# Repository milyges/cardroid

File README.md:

# cardroid
Odroid C2 and STM32F103 based, car computer for Renault Megane

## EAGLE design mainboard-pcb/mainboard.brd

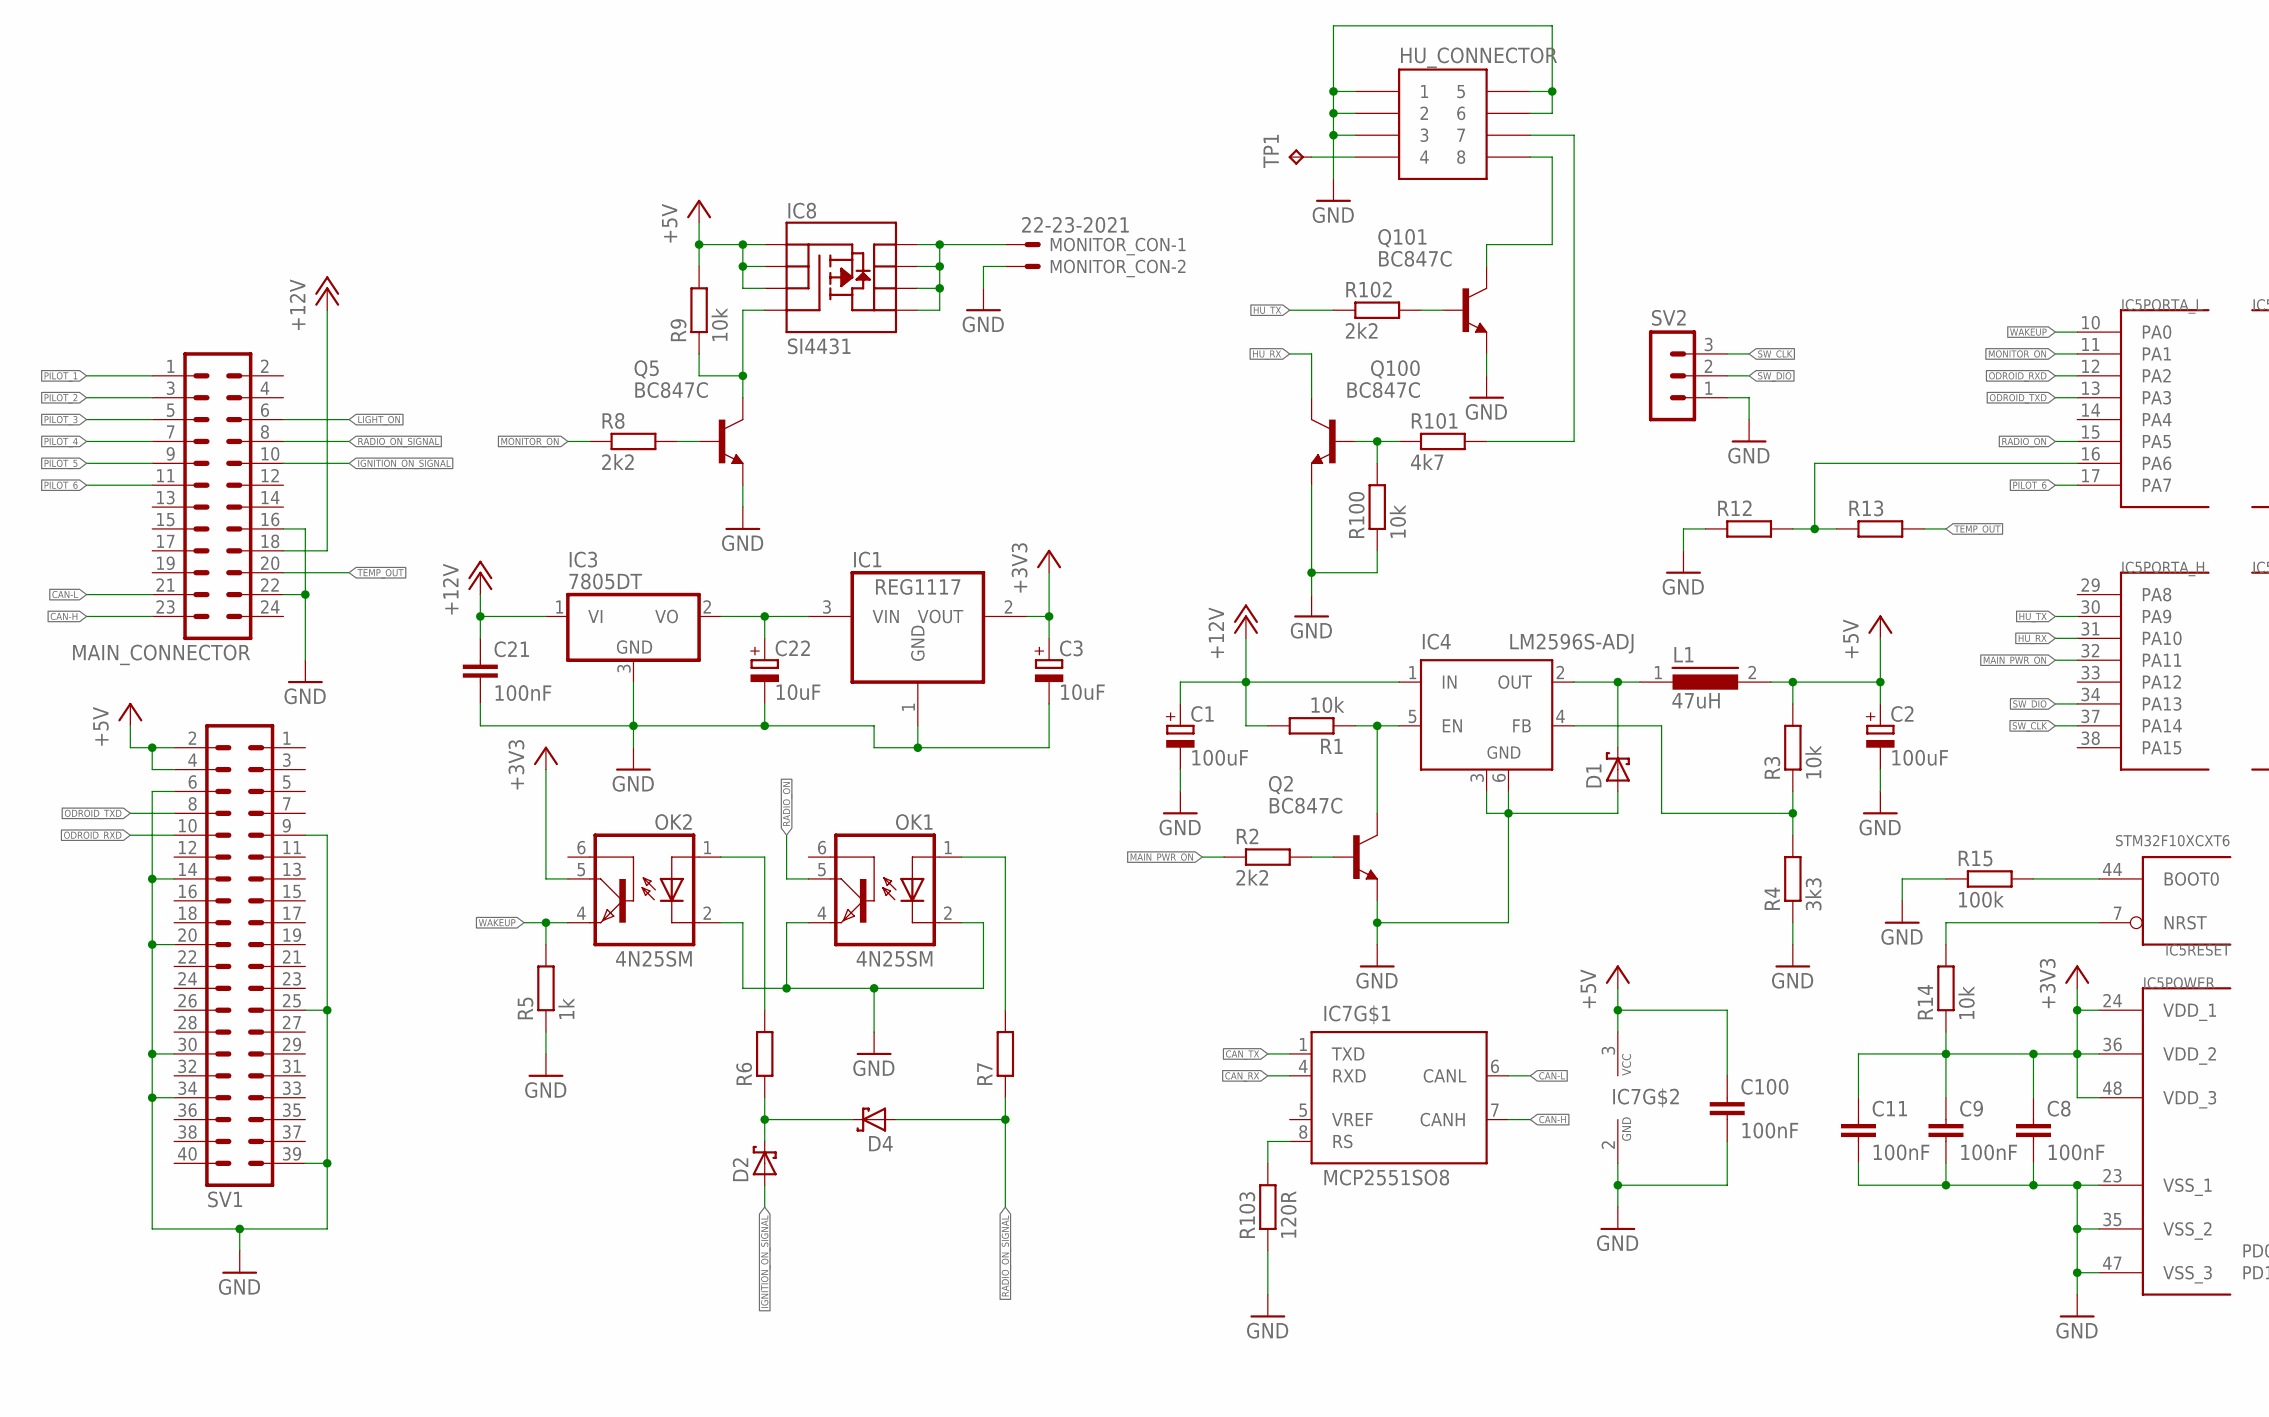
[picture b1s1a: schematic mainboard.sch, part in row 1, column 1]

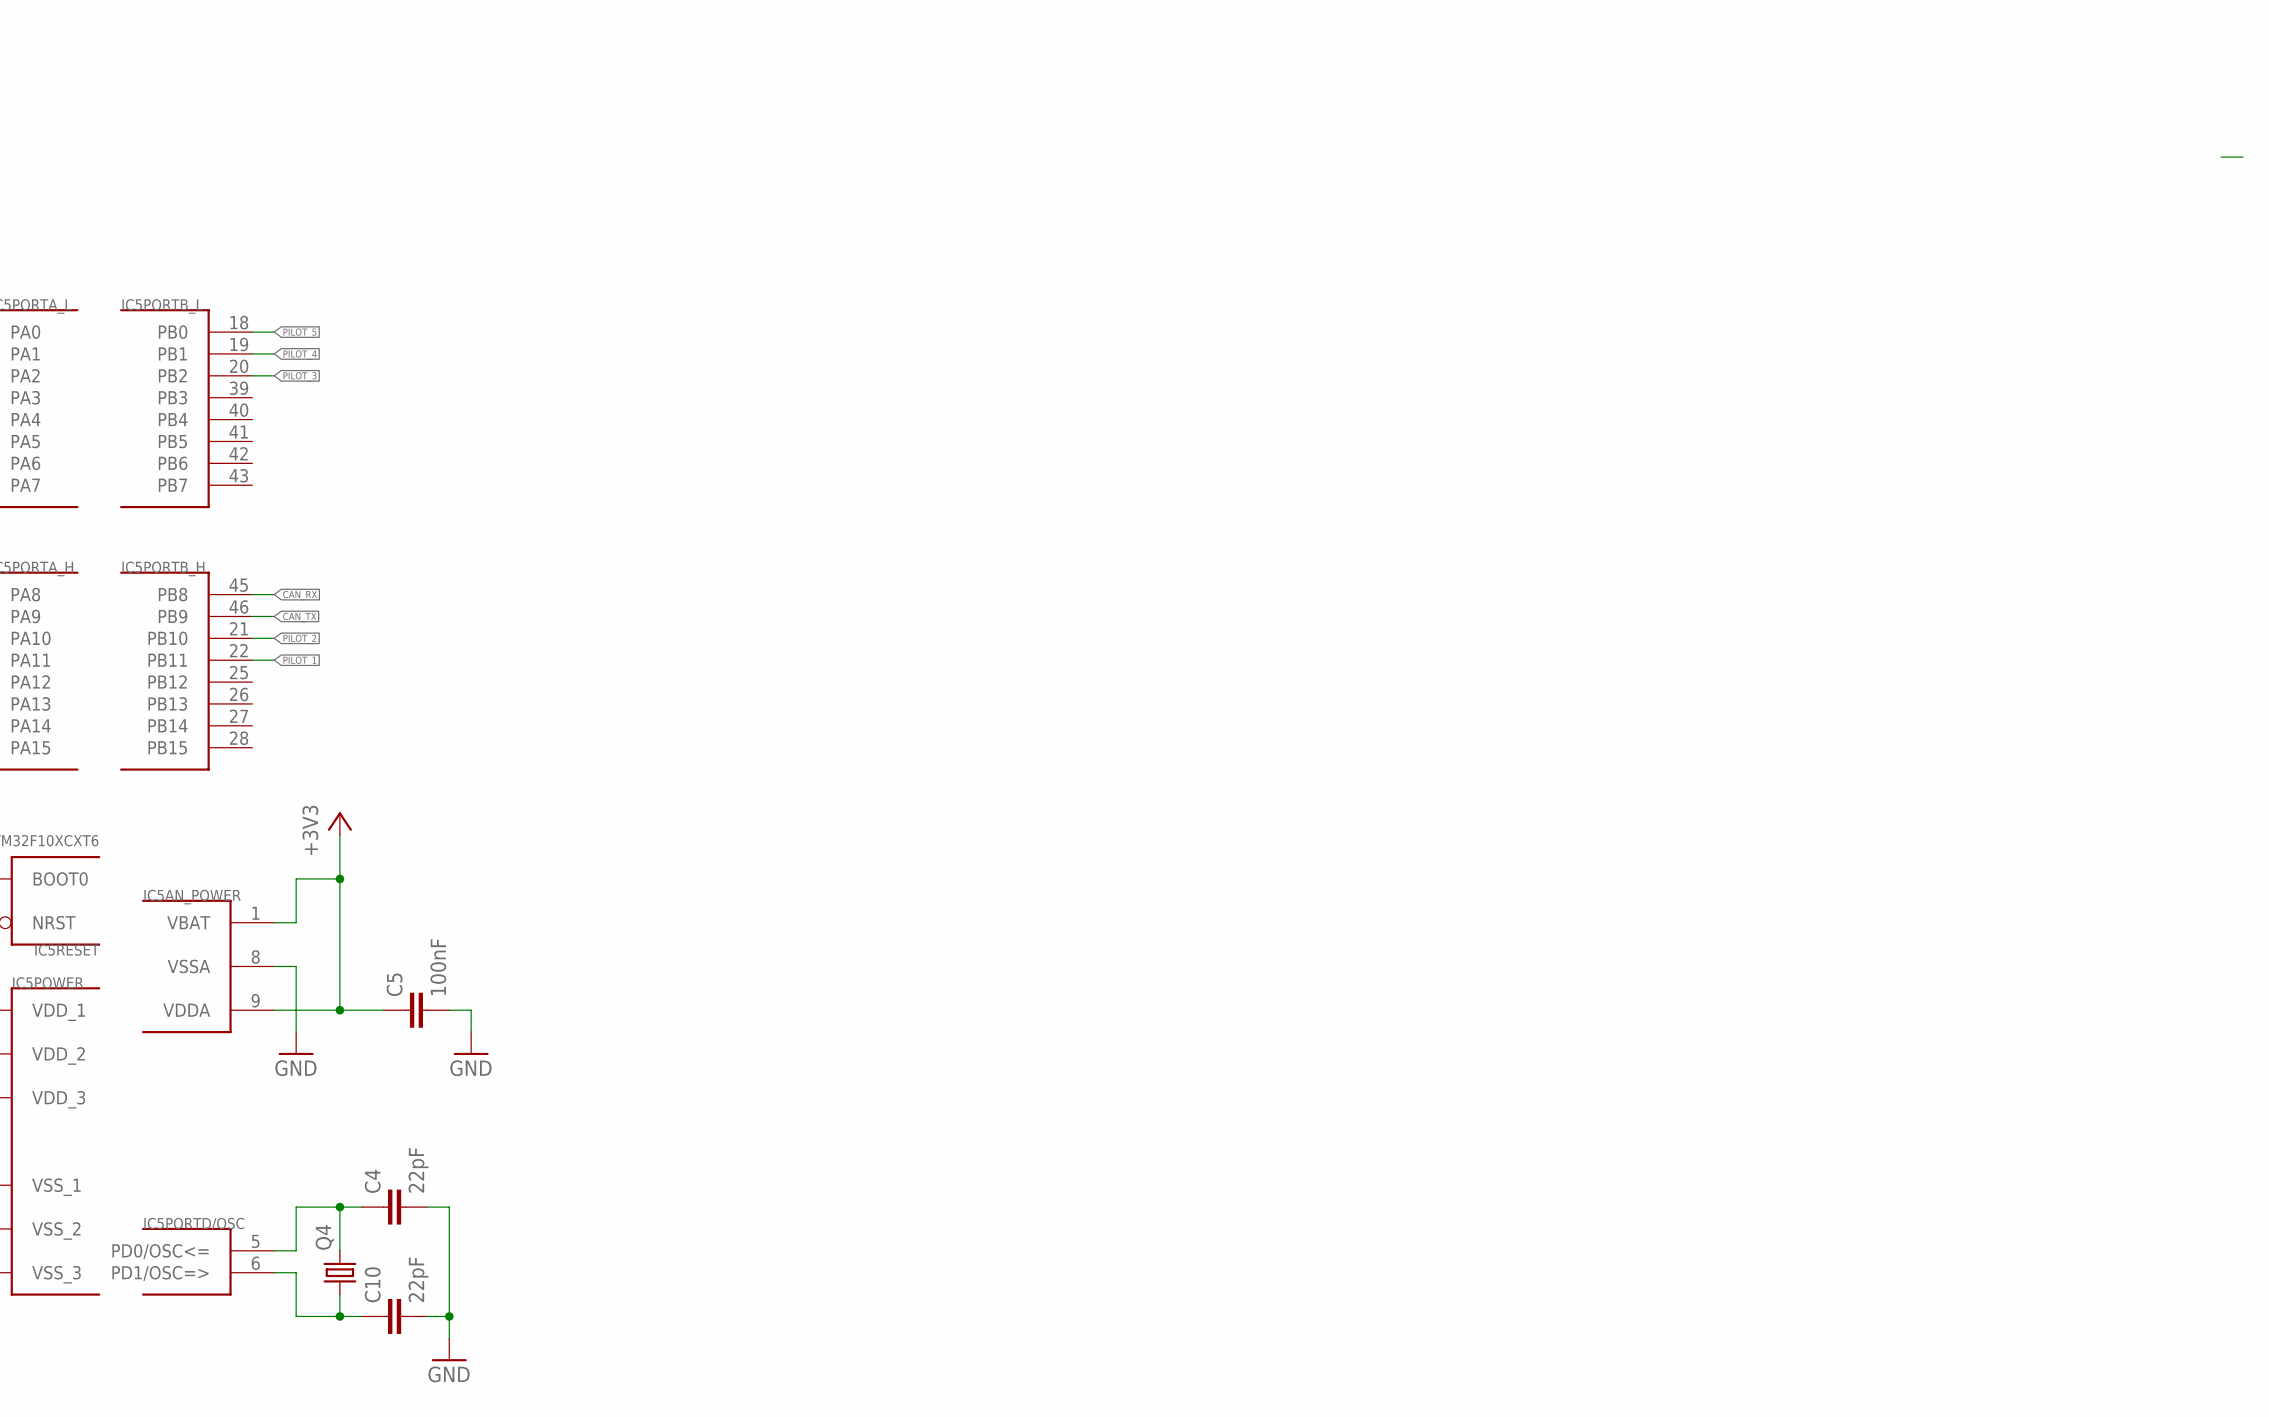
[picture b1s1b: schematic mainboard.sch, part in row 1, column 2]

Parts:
C1, C2: 100uF; 153CLV-0807
C3, C22: 10uF; SMC_A
C4, C10: 22pF; C0805
C5: 100nF; C0603
C8, C9, C11, C21, C100: 100nF; C0805
D1, D2, D4: SCHOTTKY-DIODESMD; SMB
HU_CONNECTOR: MRX56908CV; MRX56908
IC1: REG1117; SOT223
IC3: 7805DT; TO252
IC4: LM2596S-ADJ; TO263-5
IC5: STM32F10XCXT6; TQFP48
IC7: MCP2551SO8; SO08
IC8: SI4431; SO08
L1: 47uH; DR125
MAIN_CONNECTOR: MA12-2
MONITOR_CON: 22-23-2021
OK1, OK2: 4N25SM; DIL6-SMD
Q2, Q5, Q100, Q101: BC847C; SOT23-BEC
Q4: CRYSTALHC49UP; HC49UP
R1, R3, R9, R14, R100: 10k; M0805
R2, R8, R102: 2k2; M0805
R4: 3k3; M0805
R5: 1k; M0805
R6, R7, R12, R13: R-EU_M0805; M0805
R15: 100k; M0805
R101: 4k7; M0805
R103: 120R; R0805
SV1: MA20-2
SV2: MA03-1
TP1: TPPAD1-13; P1-13

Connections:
+3V3: C3.+, C5.1, C8.1, C9.1, C11.1, IC1.2 (VOUT), IC5.1 (VBAT), IC5.9 (VDDA), IC5.24 (VDD_1), IC5.36 (VDD_2), IC5.48 (VDD_3), OK2.5 (COL), R14.1
+5V: C2.+, C100.1, IC7.3 (VCC), IC8.1 (S), IC8.2 (S), IC8.3 (S), L1.2, R3.2, R9.2, SV1.2, SV1.4
+5V_CONST: C22.+, IC1.3 (VIN), IC3.2 (VO)
+12V: C1.+, C21.1, IC3.1 (VI), IC4.1 (IN), MAIN_CONNECTOR.18, R1.2
CAN-H: IC7.7 (CANH), MAIN_CONNECTOR.23
CAN-L: IC7.6 (CANL), MAIN_CONNECTOR.21
CAN_RX: IC5.45 (PB8), IC7.4 (RXD)
CAN_TX: IC5.46 (PB9), IC7.1 (TXD)
GND: C1.-, C2.-, C3.-, C4.2, C5.2, C8.2, C9.2, C10.2, C11.2, C21.2, C22.-, C100.2, D1.A, HU_CONNECTOR.P1 (1), HU_CONNECTOR.P2 (2), HU_CONNECTOR.P3 (3), HU_CONNECTOR.P5 (5), HU_CONNECTOR.P6 (6), IC1.1 (GND), IC3.3 (GND), IC4.3 (GND), IC4.6 (GND), IC5.8 (VSSA), IC5.23 (VSS_1), IC5.35 (VSS_2), IC5.47 (VSS_3), IC7.2 (GND), MAIN_CONNECTOR.16, MAIN_CONNECTOR.22, MONITOR_CON.2, OK1.2 (C), OK1.4 (EMI), OK2.2 (C), Q2.E, Q5.E, Q100.E, Q101.E, R4.1, R5.1, R12.1, R15.1, R100.1, R103.1, SV1.6, SV1.9, SV1.14, SV1.20, SV1.25, SV1.30, SV1.34, SV1.39, SV2.1
HU_RX: IC5.31 (PA10), Q100.C
HU_TX: IC5.30 (PA9), R102.1
IGNITION_ON_SIGNAL: D2.A, MAIN_CONNECTOR.10
LIGHT_ON: MAIN_CONNECTOR.6
MAIN_PWR_ON: IC5.32 (PA11), R2.1
MONITOR_ON: IC5.11 (PA1), R8.1
unnamed: IC7.8 (RS), R103.2
unnamed: IC5.16 (PA6), R12.2, R13.1
unnamed: C4.1, IC5.5 (PD0/OSC<=), Q4.2
unnamed: D1.C, IC4.2 (OUT), L1.1
unnamed: IC4.5 (EN), Q2.C, R1.1
unnamed: Q2.B, R2.2
unnamed: IC4.4 (FB), R3.1, R4.2
unnamed: IC5.7 (NRST), R14.2
unnamed: IC8.5 (D), IC8.6 (D), IC8.7 (D), IC8.8 (D), MONITOR_CON.1
unnamed: C10.1, IC5.6 (PD1/OSC=>), Q4.1
unnamed: Q101.B, R102.2
unnamed: OK2.1 (A), R6.2
unnamed: OK1.1 (A), R7.2
unnamed: D2.C, D4.C, R6.1
unnamed: IC5.44 (BOOT0), R15.2
unnamed: HU_CONNECTOR.P7 (7), R101.2
unnamed: Q100.B, R100.2, R101.1
unnamed: HU_CONNECTOR.P8 (8), Q101.C
unnamed: Q5.B, R8.2
unnamed: IC8.4 (G), Q5.C, R9.1
ODROID_RXD: IC5.12 (PA2), SV1.10
ODROID_TXD: IC5.13 (PA3), SV1.8
PILOT_1: IC5.22 (PB11), MAIN_CONNECTOR.1
PILOT_2: IC5.21 (PB10), MAIN_CONNECTOR.3
PILOT_3: IC5.20 (PB2), MAIN_CONNECTOR.5
PILOT_4: IC5.19 (PB1), MAIN_CONNECTOR.7
PILOT_5: IC5.18 (PB0), MAIN_CONNECTOR.9
PILOT_6: IC5.17 (PA7), MAIN_CONNECTOR.11
RADIO_ON: IC5.15 (PA5), OK1.5 (COL)
RADIO_ON_SIGNAL: D4.A, MAIN_CONNECTOR.8, R7.1
SPDIF_IN: HU_CONNECTOR.P4 (4), TP1.TP
SW_CLK: IC5.37 (PA14), SV2.3
SW_DIO: IC5.34 (PA13), SV2.2
TEMP_OUT: MAIN_CONNECTOR.20, R13.2
WAKEUP: IC5.10 (PA0), OK2.4 (EMI), R5.2

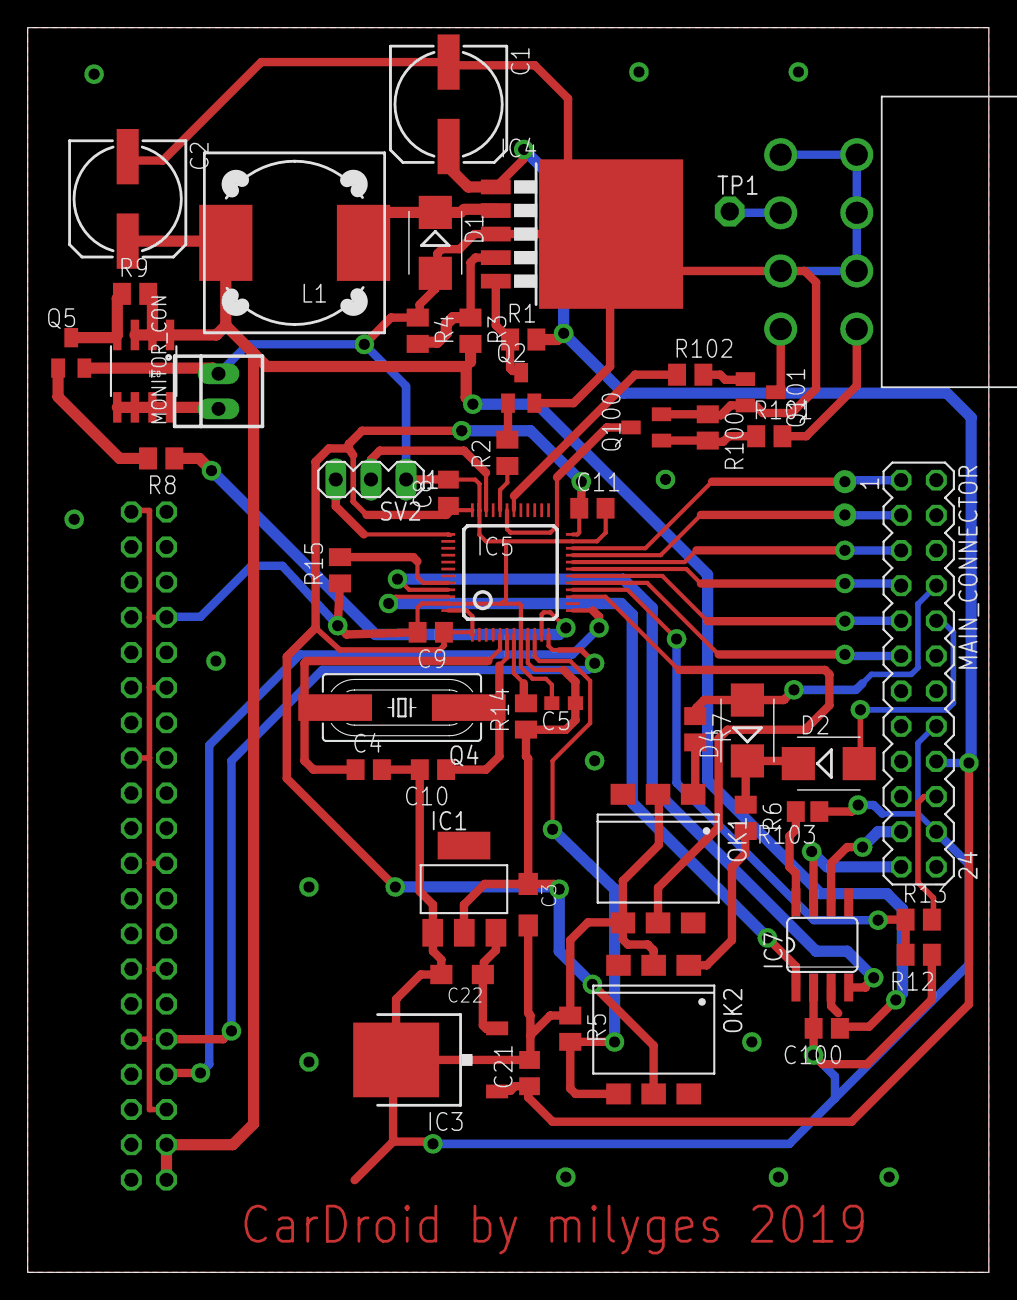
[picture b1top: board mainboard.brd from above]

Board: 2 copper layers, 69.4 x 89.9 mm, 52 parts (1 on the bottom side), 49 nets.

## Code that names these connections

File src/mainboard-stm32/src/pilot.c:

#include "stm32f10x_conf.h"
#include "pilot.h"

/*
 * Podłączenie pilota:
 * PB10 -> COL0
 * PB11 -> COL1
 * PB2  -> COL2
 * PA7  -> ROW0
 * PB1  -> ROW1
 * PB0  -> ROW2
*/
#define COL0_GPIO   GPIOB
#define COL0_PIN    GPIO_Pin_10
#define COL1_GPIO   GPIOB
#define COL1_PIN    GPIO_Pin_11
#define COL2_GPIO   GPIOB
#define COL2_PIN    GPIO_Pin_2
#define ROW0_GPIO   GPIOA
#define ROW0_PIN    GPIO_Pin_7
#define ROW1_GPIO   GPIOB
#define ROW1_PIN    GPIO_Pin_1
#define ROW2_GPIO   GPIOB
#define ROW2_PIN    GPIO_Pin_0

#define ROW_DOWN(x) GPIO_WriteBit(x ## _GPIO, x ## _PIN, Bit_RESET)
#define ROW_UP(x) GPIO_WriteBit(x ## _GPIO, x ## _PIN, Bit_SET)
#define COL_READ(x) (GPIO_ReadInputDataBit(x ## _GPIO, x ## _PIN) == Bit_SET)

static inline void _pilot_delay(void) {
	int i;
	for (i = 0; i < 4000; i++) __NOP();
}

uint8_t pilot_getkey(void) {
	int8_t roll_state = -1;
	static uint8_t old_roll_state = -1;
	uint8_t key = 0;

	ROW_DOWN(ROW0); /* Wiersz 0 - rolka */
	_pilot_delay(); /* Opóźnienie na ustabilizowanie się stanów logicznych */
	if (!COL_READ(COL0))
		roll_state = 0;
	if (!COL_READ(COL1))
		roll_state = 1;
	if (!COL_READ(COL2))
		roll_state = 2;
	ROW_UP(ROW0);

	ROW_DOWN(ROW1);
	_pilot_delay();
	if (!COL_READ(COL0))
		key |= PILOT_KEY_VOLUP;
	if (!COL_READ(COL1))
		key |= PILOT_KEY_VOLDOWN;
	if (!COL_READ(COL2))
		key |= PILOT_KEY_LOAD;
	ROW_UP(ROW1);

	ROW_DOWN(ROW2);
	_pilot_delay();
	if (!COL_READ(COL0))
		key |= PILOT_KEY_PAUSE;
	if (!COL_READ(COL1))
		key |= PILOT_KEY_SOURCE_L;
	if (!COL_READ(COL2))
		key |= PILOT_KEY_SOURCE_R;
	ROW_UP(ROW2);

	/* Obsługa rolki */
	if ((roll_state != old_roll_state) && (roll_state != -1)) {
		if (old_roll_state >= 0) {
			if (((old_roll_state + 1) % 3) == roll_state)
				key |= PILOT_ROLL_PREV;
			else
				key |= PILOT_ROLL_NEXT;
		}
		old_roll_state = roll_state;
	}
	return key;
}

void pilot_init(void) {
	GPIO_InitTypeDef gpio_initstruct;
	RCC_APB2PeriphClockCmd(RCC_APB2Periph_GPIOA | RCC_APB2Periph_GPIOB, ENABLE); /* Zegar */

	/* Kolumnty jako wejścia z podciągnięciem do VCC */
	gpio_initstruct.GPIO_Mode = GPIO_Mode_IPU;
	gpio_initstruct.GPIO_Speed = GPIO_Speed_2MHz;
	gpio_initstruct.GPIO_Pin = COL0_PIN;
	GPIO_Init(COL0_GPIO, &gpio_initstruct);
	gpio_initstruct.GPIO_Pin = COL1_PIN;
	GPIO_Init(COL1_GPIO, &gpio_initstruct);
	gpio_initstruct.GPIO_Pin = COL2_PIN;
	GPIO_Init(COL2_GPIO, &gpio_initstruct);

	/* Wiersze jako wyjścia Open Drain */
	gpio_initstruct.GPIO_Mode = GPIO_Mode_Out_OD;
	gpio_initstruct.GPIO_Speed = GPIO_Speed_2MHz;
	gpio_initstruct.GPIO_Pin = ROW0_PIN;
	GPIO_Init(ROW0_GPIO, &gpio_initstruct);
	gpio_initstruct.GPIO_Pin = ROW1_PIN;
	GPIO_Init(ROW1_GPIO, &gpio_initstruct);
	gpio_initstruct.GPIO_Pin = ROW2_PIN;
	GPIO_Init(ROW2_GPIO, &gpio_initstruct);
	ROW_UP(ROW0);
	ROW_UP(ROW1);
	ROW_UP(ROW2);
}

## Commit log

2019-03-30 Import źródeł dla mikrokontrolera
2019-03-30 Import aplikacji na androida
2019-03-30 Import schematu
2019-03-30 Implementacja obsługi pilota pod kierownicą
2019-03-31 Implementacja emulatora zmieniarki
2019-03-31 dodanie sprawdzania checksum w cdcemu i resetu CANa w displayemu
2019-04-03 Dodanie synchronizacji czasu z GPS i zarządzania zasilaniem ekranu
2019-04-06 Zarządzanie zasilaniem ekranu, ikonki stanu połączenia bluetooth i internetu
2019-04-18 Przygotowania do uruchomienia wskaźników, poprawki w obsłudze bluetooth
2020-02-16 Dodanie obsługi regulacji jasności ekranu, watchdoga i poprawki błędów
2021-09-20 Poprawki i ulepszenia
